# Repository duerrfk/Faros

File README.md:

Faros is a Bluetooth Low Energy (BLE) beacon supporting Google's open beacon 
format Eddystone [1]. As hardware platform, Faros uses Arduino and the nRF8001 
BLE chip by Nordic Semiconductors [2].

The main features are:

* Full support for all Eddystone frame types (UID, URL, TLM)
* Energy efficiency allowing for runtimes of several years
* Using popular and powerful hardware platforms: Arduino and nRF8001 BLE chip
* Simplicity of hardware: easy to build using a commodity Arduino or our
  Faros board together with the BLE module MOD-nRF8001 from Olimex [3]
* Liberal licensing: Apache License 2.0 for software, CERN Open Hardware 
  Licence v1.2 for hardware 

The following images show a self-etched Faros board and a Faros board
manufactured by a PCB manufacturer.

This project includes:

* Source code for Arduino
* Faros board schematics and board layouts

# Source Code

## Prerequisites

To compile the code, you need the Arduino IDE (tested with version 1.6.5).

Moreover, you need the Arduino BLE SDK from Nordic Semiconductors available 
from GitHub:

https://github.com/NordicSemiconductor/ble-sdk-arduino

1. Download SDK: `git clone https://github.com/NordicSemiconductor/ble-sdk-arduino.git`
2. Start the Arduino IDE (tested with v1.6.5)
3. Import the library: select `Sketch/Import library/Add` library and 
   then choose folder `libraries/BLE` from the downloaded SDK.
4. Check the availability of the library. There should be an entry `BLE`
   in menu `Sketch/Import library`.

The BLE services of nRF8001 are configured by the freely available nRFgo 
Studio tool (Windows application) [5]. This tool generates a file 
(`services.h`), which is also included in the repository. Thus, you  
only need to install this tool if you want to modify the BLE service 
description for some reason. The data of Eddystone frames is defined in the 
source code.

You also need the BLE module MOD-nRF8001 from Olimex [3]. Earlier versions 
of this module used the "C" revision of the nRF8001, which does not support
broadcasting data! So you need a module with the "D" revision of the nRF8001.
According to Olimex, all modules sold now have the "D" revision of the
nRF8001.

Since the nRF8001 module is specified for a voltage range of 1.9 V - 3.6 V, 
you should use an Arduino with suitable voltage levels. For instance, 
Arduino UNO uses 5 V, so you would have to shift levels when connecting to 
nRF8001. We tested with a 3.3 V Arduino Pro Micro and the Faros board
whose design is also included in this repository.
 
## Adapting the Source Code

If you use the Faros board or Arduino Pro Micro, you can simply
set the following definitions at the beginning of the sketch.

For the Faros board:

    #define HARDWARE_ATMEGA328P_1MHz

For Arduino Pro Micro:

    #define HARDWARE_ATMEGA32U4_8MHz

For those who are interested in the technical details: The Arduino communicates
with the nRF8001 through SPI. Beyond the standard SPI pins (MISO, MOSI, SCK, 
SS), the nRF8001 uses another select pin (called RDYN) to signal that the 
nRF8001 has events to be sent to the Arduino. Moreover, the reset pin (RST) of 
the nRF8001 has to be connected. Thus, we need 6 pins to connect the Arduino 
to the nRF8001:

1. MISO
2. MOSI
3. SCK
4. REQN/SS
5. RDYN
7. RST

For the standard SPI pins, select the usual pins depending on your Arduino.
RDYN should be assigned to a pin with a hardware interrupt. We use this 
interrupt to wake up the Arduino from power-down mode when the nRF8001 wants
to send an event to the Arduino.

For the Arduino Pro Micro, we used the following pins according to the
Arduino numbering scheme:

* MISO = 14
* MOSI = 16
* SCK = 15
* REQN/SS = 7
* RDYN = 3 -> INT0
* RST = 4

For the Faros board based on ATmega328P, we used the following pins (Arduino 
numbering scheme; ATmega names are given in brackets):

* MISO = 12 (PB4)
* MOSI = 11 (PB3)
* SCK = 13 (PB5)
* REQN/SS = 10 (PB2)
* RDYN = 2 (PD2) -> INT0
* RST = 3 (PD3)

Moreover, nRF8001 supports a maximum SPI clock frequency of 3 MHz. To adjust the
SPI clock frequency, set the definition SPI_CLOCK_DIV according to your 
platform. For instance, the Arduino Pro Micro is running at 8 MHz, so we need 
to divide it by 4 (SPI_CLOCK_DIV4) to get 2 MHz. The Faros board uses an 
ATmega328P at 1 MHz, so theoretically we could divide by 1. However, the 
smallest divider available for ATmega is 2 (SPI_CLOCK_DIV2), so we will run at 
500 kHz SPI clock.

Finally, you need to set your specific data to be broadcasted by the beacon.
Eddystone supports the following data:

* UID frames:
    * beacon ID consisting of namespace id and instance id
    * TX power level
* URL frame: 
    * short URL 
    * TX power level
* TLM frame: 
    * battery level
    * temperature
    * uptime
    * number of broadcasted frames since boot

You need to set the data for UID and URL frames through variables at the 
beginning of the sketch. The data for TLD frames is detected automatically 
(nRF8001 features a temperature sensor and voltage sensor).

Moreover, you can select whether you want to send UID and/or URL frames 
and/or TLM frames by setting the variables `is_enabled_uid`, `is_enabled_url`, 
and `is_enabled_tlm`, respectively. The beacon will cycle through all 
enabled frames, so it can send UID frames, URL frames, and TLM frames 
(sequentially).

# Hardware: The Faros Board

If you just want to experiment, you can simply use a commodity Arduino 
running at 3.3 V like the Arduino Pro Micro. Just directly connect the pins
of the Arduino Pro Micro and the BLE module like this:

* MISO = 14
* MOSI = 16
* SCK = 15
* REQN/SS = 7
* RDYN = 3 -> INT0
* RST = 4

However, if you want to deploy beacons in the field, two requirements become 
essential:

* Energy efficiency: the beacon must run from battery for several years 
* Cost: if you want to deploy many beacons, a commodity Arduino board
  is too expensive

The Faros board tries to fulfill these requirements plus one more: keep
things as simple as possible so virtually everyone can build a Faros
beacon.

The Faros board uses an ATmega328P together with the BLE module MOD-nRF8001 
from Olimex [3] based on the nRF8001 chip from Nordic Semiconductors. We 
selected the nRF8001 for several reasons:

* Easy to connect to Arduino through SPI
* Open Arduino SDK [4]
* Includes temperature sensor (required for TLM frames)
* Includes voltage sensor (required for TLM frames)

The BLE module MOD-nRF8001 from Olimex provides a ready-to-use solution to use
the nRF8001 together with the Arduino.

The Faros board is kept as simple as possible (through-hole design, no SMD 
components). It comes in two variants: (1) a single-sided 50 mm x 70 mm layout 
that is well-suited for self-etching (a PDF of the layout can be found in 
folder `pcb`); (2) a double-sided 50 mm x 50 mm layout that can be sent to a 
PCB manufacturer (the Gerber files can be found in folder `gerber`). For both 
variants, the ATmega is programmed using ISP, so no USB is required which 
again saves cost and energy. Moreover, we use the ATmega's internal RC 
oscillator, so no external crystal is required. 

Here is the bill of material for the Faros board:

* C1, C2, C3: 100 nF (ceramic capacitor, X7R, 5.08 pitch)
* LED1: 3 mm
* R1: 10 k Ohm
* R2: 100 Ohm
* R3, R4, R5: 4.7 k Ohm
* IC1: ATmega328P-PU
* MOD1: Olimex MOD-nRF8001
* SV1: 3x2 pin header (2.54 pitch)
* X1: screw terminal (5.08 pitch)

## Programming the Faros Board

The Faros board is programmed via ISP. The 6 pin ISP6 connector has the usual 
layout:

    MISO <-- 1 2 --> VCC
     SCK <-- 3 4 --> MOSI
     RST <-- 5 6 --> GND

You can leave the BLE module connected while programming the ATmega (the 
4.7 k resistors shield the SPI pins of the nRF8001 during programming). However,
you should use a 3.3 V programmer since the maximum voltage of the nRF8001
is 3.6 V.

To preprare the ATmega328P, program the following fuses (note that "0" means 
that the fuse is programmed):

* CKSEL = 0010: use internal 8 MHz RC oscillator
* CKDIV8 = 0: 1 MHz system clock (dividing the 8 MHz internal clock by 8)
* SPIEN = 0: enable serial programming
* BODLEVEL = 110: brown-out detection set to 1.8 V
* SUT = 00: lowest possible startup time (6 CK from power-down; since we use
  BOD, we do not need additional waiting time for the power source to come up)
    
Using avrdude, the command looks like this (note: under Linux you might need
to execute this command as root depending on your programmer):

    $> avrdude -c usbasp -p m328p -U lfuse:w:0x42:m -U hfuse:w:0xd9:m -U efuse:w:0x06:m

Then, we compile and write the program to the ATmega. Before compiling the 
program, make sure you have adapted the pins (see above), SPI clock divider 
(see above), and to generate code for an ATmega at 1 MHz. In the repository, 
you will find a suitable board definition for the Arduino IDE (see folder 
`board_definition`). Copy the directory `faros-atmega` into the folder 
`hardware` in your Arduino sketchbook. Then you should find and select the 
board  called `Faros ATMega 328P @ 1 MHz` under the menu item `Tools/Board`. 

Compiling generates a hex file that we need to program the ATmega. This hex 
file is a little bit hidden in the temporary build directory of the Arduino
IDE. If you use Linux  and Arduino IDE 1.6, have a look at the `/tmp` 
directory. After hitting the  compile button in the Arduino IDE, search for the
latest hex file called  `faros.cpp.hex` in a temporary directory named 
`/tmp/build...`. If you have found the hex file, you can write it using avrdude
(again, you might need root right):

    $> avrdude -p m328p -c usbasp -v -U flash:w:faros.cpp.hex
 
## Saving Energy

The basic method to save energy is to minimize the duty cycle. Therefore,
we put the ATmega into power-down mode (deepest power-saving mode) as long as
possible, and only wake it up, when some work has to be done. This can either
be an event from the nRF8001 module , which triggers a hardware interrupt on
the RDYN pin. Or it can be a timer event from the watch dog timer (which
keeps running in power-down mode in contrast to the other timers). By switching
of the ADC and disabling brown-out detecting while sleeping (only possible
with the ATmega328P, not with the ATmega328), the ATmega328P only consumes 
a few uA (actually, the "P" in 328P means "pico-power"). 

Another important design choice is the type of battery. The nRF8001 
can run down to 1.9 V; the ATmega down to 1.8 V at frequencies <= 4 MHz. The 
maximum voltage for the nRF8001 is 3.6 V. Thus, one good option is to use two 
AA or AAA size alkaline batteries. They are cheap. They provide > 1800 mAh, 
which should suffice for several years of runtime. They are discharged at about 
1.0 V (then the voltage drops rapidly), which fits nicely our desired voltage 
range of 1.9 - 3.0 V. And at runtimes of several years, no re-charging is
required (you rather replace the device than changing the batteries). Of 
course, you can also try out other options like coin cells (e.g., one 
CR 2450 @ 3.0 V, 560 mAh), or one battery (1.5 V) plus a step-up converter 
(which wastes maybe more than 20 % energy for conversion and is probably more
expensive than a second AA or AAA battery).

The board also has a 3 mm low-current LED, which can be switched on by digital 
pin 4 of the Arduino. With a resistor of 100 Ohm, it draws 10 mA at 3 V, which 
is a lot if we target runtimes of several years! So if you aim at maximum 
battery lifetime, only send short pulses in long intervals (e.g., one 100 ms 
pulse every 30 s amounts to about 33 uA average current), or even better: rely 
on TLM frames.

# Testing

In order to test that your beacon works, you need a client, e.g., a mobile
phone or tablet with BLE and an application that understands Eddystone
beacons. There are (at least) two nice apps for Android that show all the
details of the three types of Eddystone frames:

* nRFMaster Control Panel by Nordic Semiconductors [6]
* Eddystone Validator by Google (requires Android 5 aka. Lollipop) [7]

Faros is cycling through all frame types (if you have enabled all of them)
and switches to a new frame type every second. So after about 3 seconds you 
should see the data of all three frame types (most interesting is maybe
the TLM type since its data changes dynamically).

# Licensing

Faros uses two licenses for open hardware and software, respectively:

* The software (source code) is licensed under the Apache License 2.0 [8]
* The hardware (schematic diagrams, circuit board layouts, hardware
  documentation) is licensed under the CERN Open Hardware Licence v1.2 [9]

Both licenses are also included in the repository.

# References

* [1] https://developers.google.com/beacons/
* [2] https://www.nordicsemi.com/eng/Products/Bluetooth-Smart-Bluetooth-low-energy/nRF8001 
* [3] https://www.olimex.com/Products/Modules/RF/MOD-nRF8001/
* [4] https://github.com/NordicSemiconductor/ble-sdk-arduino
* [5] https://www.nordicsemi.com/chi/node_176/2.4GHz-RF/nRFgo-Studio
* [6] https://www.nordicsemi.com/eng/Products/nRFready-Demo-Apps/nRF-Master-Control-Panel-application
* [7] https://github.com/google/eddystone
* [8] http://www.apache.org/licenses/LICENSE-2.0
* [9] http://www.ohwr.org/attachments/2388/cern_ohl_v_1_2.txt

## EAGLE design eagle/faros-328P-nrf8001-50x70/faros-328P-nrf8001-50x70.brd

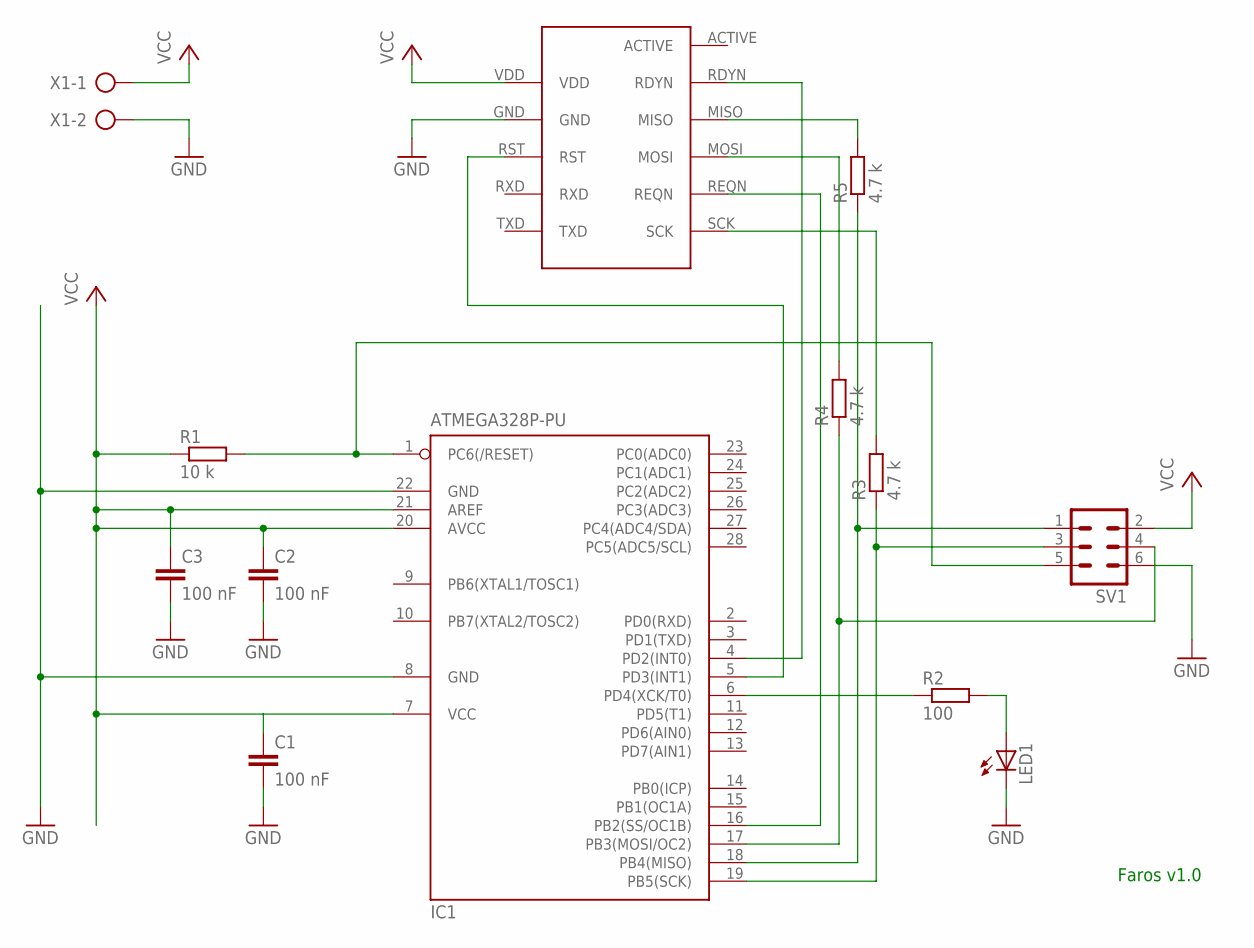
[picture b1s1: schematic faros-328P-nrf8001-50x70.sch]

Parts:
C1, C2, C3: 100 nF; C050-024X044
IC1: ATMEGA328P-PU; DIL28-3
LED1: LED3MM
MOD1: MOD-NRF8001MOD-NRF8001; MOD-NRF8001
R1: 10 k; 0207/7
R2: 100; 0207/7
R3, R4, R5: 4.7 k; 0207/7
SV1: MA03-2
X1: AK500/2

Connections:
GND: C1.2, C2.2, C3.2, IC1.8 (GND), IC1.22 (GND), LED1.K (C), MOD1.GND, SV1.6, X1.2
unnamed: IC1.4 (PD2(INT0)), MOD1.RDYN
unnamed: IC1.19 (PB5(SCK)), R3.1, SV1.3
unnamed: IC1.1 (PC6(/RESET)), R1.2, SV1.5
unnamed: MOD1.MOSI, R4.2
unnamed: MOD1.MISO, R5.2
unnamed: IC1.5 (PD3(INT1)), MOD1.RST
unnamed: LED1.A, R2.2
unnamed: IC1.6 (PD4(XCK/T0)), R2.1
unnamed: MOD1.SCK, R3.2
unnamed: IC1.16 (PB2(SS/OC1B)), MOD1.REQN
unnamed: IC1.18 (PB4(MISO)), R5.1, SV1.1
unnamed: IC1.17 (PB3(MOSI/OC2)), R4.1, SV1.4
VCC: C1.1, C2.1, C3.1, IC1.7 (VCC), IC1.20 (AVCC), IC1.21 (AREF), MOD1.VDD, R1.1, SV1.2, X1.1

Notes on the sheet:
Faros v1.0

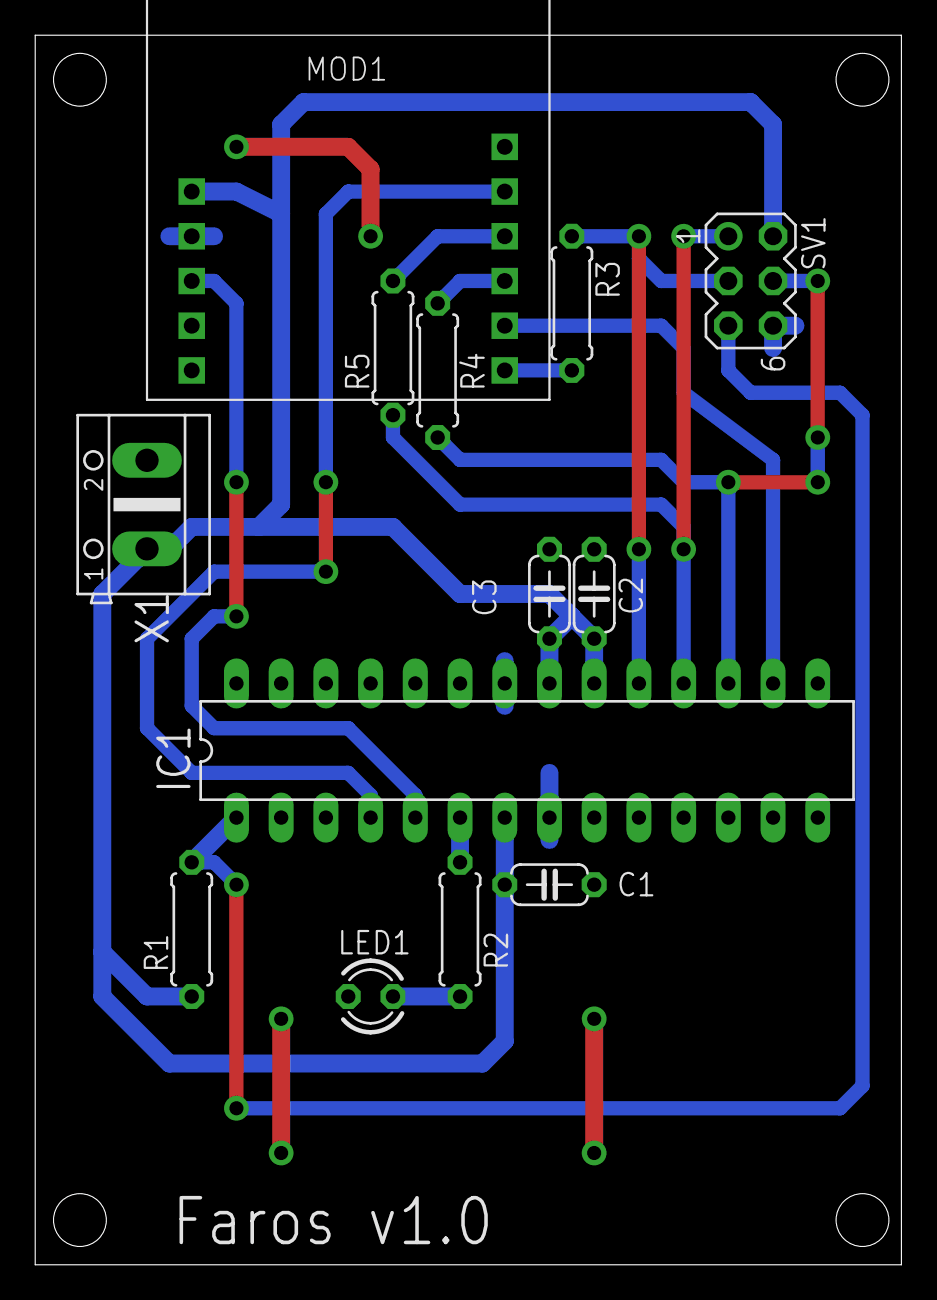
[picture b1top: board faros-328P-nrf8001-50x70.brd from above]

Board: 2 copper layers, 49.2 x 69.8 mm, 13 parts (0 on the bottom side), 14 nets.

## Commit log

2015-08-27 Initial check-in
2015-08-28 Added PDF of schematic.
2015-08-28 Increased min. restring sizes and improved clearance
2015-08-29 Added 50x50 double-sided layout for PCB manufacturer
2015-08-30 Cleaned up part names. Added BOM to readme. Added PDF showing part placement for single-sided board. Updated Gerber files and PCB layout (PDF).
2015-08-30 Added gerber files
2015-08-30 Added wires in parts-and-places PDF
2015-09-10 Added CERN Open Hardware License for the hardware part.
2015-09-10 Consistent file naming
2015-10-03 Added definitions at beginning of sketch to make selection of board easy
2015-10-03 Moved clock divider into board specific sections
2015-10-11 Added images
2016-05-05 Removed Eagle project files (not required)
